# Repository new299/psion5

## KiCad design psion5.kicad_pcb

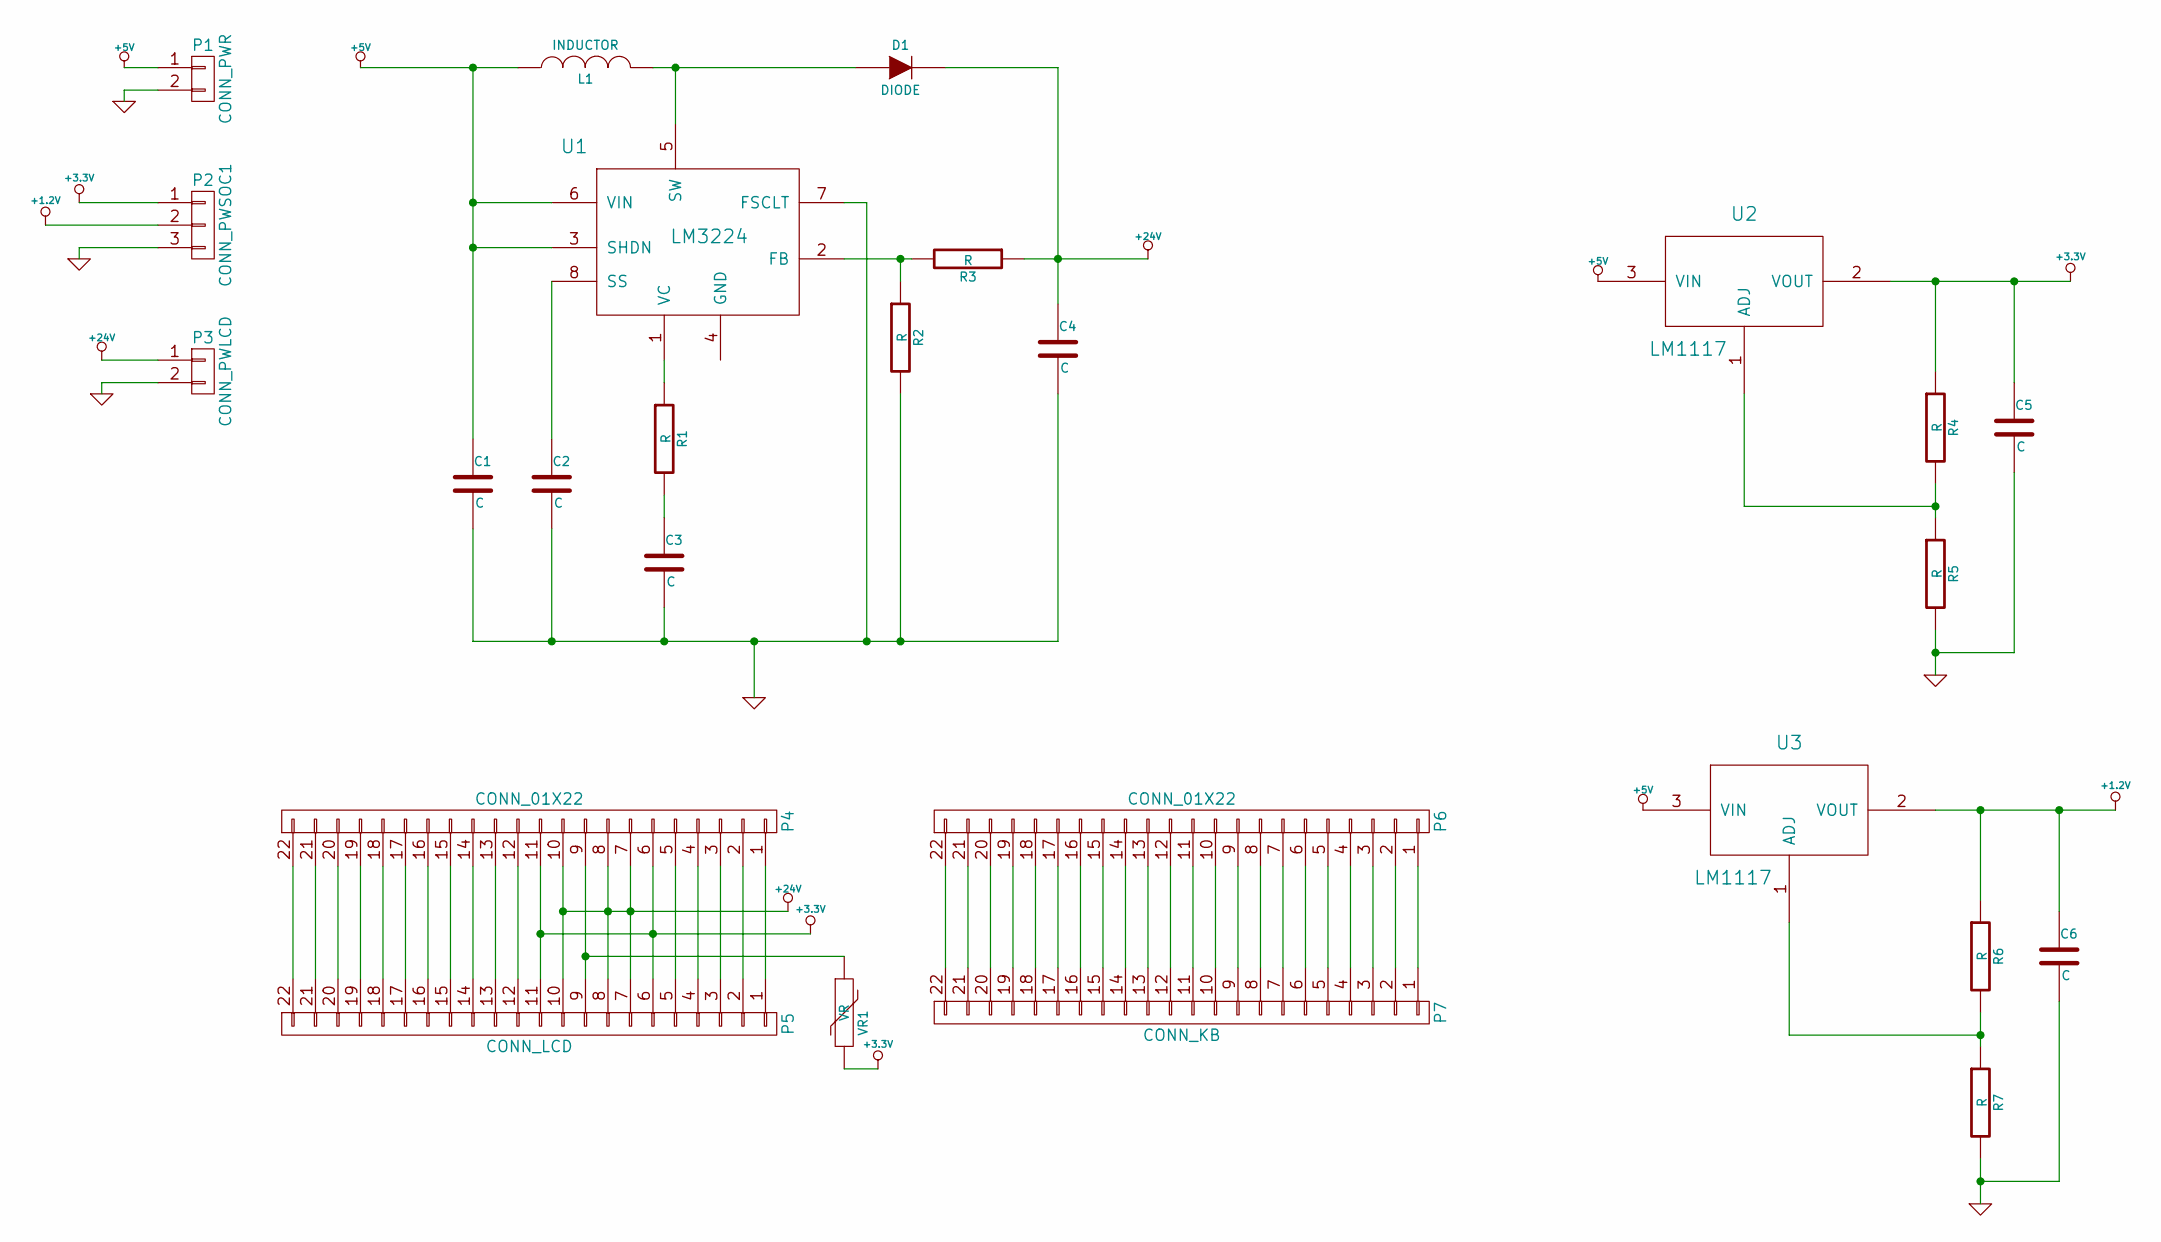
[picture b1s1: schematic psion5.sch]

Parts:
C1, C2, C3, C4, C5, C6: C; c_1206
D1: DIODE; Diode-MELF_Standard
L1: INDUCTOR; Neosid_Inductor_SMs42
P1: CONN_PWR; Socket_Strip_Straight_1x02
P2: CONN_PWSOC1; Socket_Strip_Straight_1x03
P3: CONN_PWLCD; Socket_Strip_Straight_1x02
P4, P6: CONN_01X22; Socket_Strip_Straight_1x22
P5: CONN_LCD; FPC22
P7: CONN_KB; FPC22
R1, R2, R3, R4, R5, R6, R7: R; R_1206
U1: LM3224; SSOP-8
U2, U3: LM1117; sot89
VR1: VR; R_1210

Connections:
+1.2V: C6.1, P2.2, R6.1, U3.2 (VOUT)
+3.3V: C5.1, P2.1, P4.6, P4.11, P5.6, P5.11, R4.1, U2.2 (VOUT), VR1.2
+5V: C1.1, L1.1, P1.1, U1.3 (SHDN), U1.6 (VIN), U2.3 (VIN), U3.3 (VIN)
+24V: C4.1, D1.2 (K), P3.1, P4.7, P4.8, P4.10, P5.7, P5.8, P5.10, R3.1
GND: C1.2, C2.2, C3.2, C4.2, C5.2, C6.2, P1.2, P2.3, P3.2, R2.2, R5.2, R7.2, U1.7 (FSCLT)
unnamed: C2.1, U1.8 (SS)
unnamed: C3.1, R1.2
unnamed: D1.1 (A), L1.2, U1.5 (SW)
unnamed: P4.1, P5.1
unnamed: P4.2, P5.2
unnamed: P4.3, P5.3
unnamed: P4.4, P5.4
unnamed: P4.5, P5.5
unnamed: P4.9, P5.9, VR1.1
unnamed: P4.12, P5.12
unnamed: P4.13, P5.13
unnamed: P4.14, P5.14
unnamed: P4.15, P5.15
unnamed: P4.16, P5.16
unnamed: P4.17, P5.17
unnamed: P4.18, P5.18
unnamed: P4.19, P5.19
unnamed: P4.20, P5.20
unnamed: P4.21, P5.21
unnamed: P4.22, P5.22
unnamed: P6.1, P7.1
unnamed: P6.2, P7.2
unnamed: P6.3, P7.3
unnamed: P6.4, P7.4
unnamed: P6.5, P7.5
unnamed: P6.6, P7.6
unnamed: P6.7, P7.7
unnamed: P6.8, P7.8
unnamed: P6.9, P7.9
unnamed: P6.10, P7.10
unnamed: P6.11, P7.11
unnamed: P6.12, P7.12
unnamed: P6.13, P7.13
unnamed: P6.14, P7.14
unnamed: P6.15, P7.15
unnamed: P6.16, P7.16
unnamed: P6.17, P7.17
unnamed: P6.18, P7.18
unnamed: P6.19, P7.19
unnamed: P6.20, P7.20
unnamed: P6.21, P7.21
unnamed: P6.22, P7.22
unnamed: R1.1, U1.1 (VC)
unnamed: R2.1, R3.2, U1.2 (FB)
unnamed: R4.2, R5.1, U2.1 (ADJ)
unnamed: R6.2, R7.1, U3.1 (ADJ)

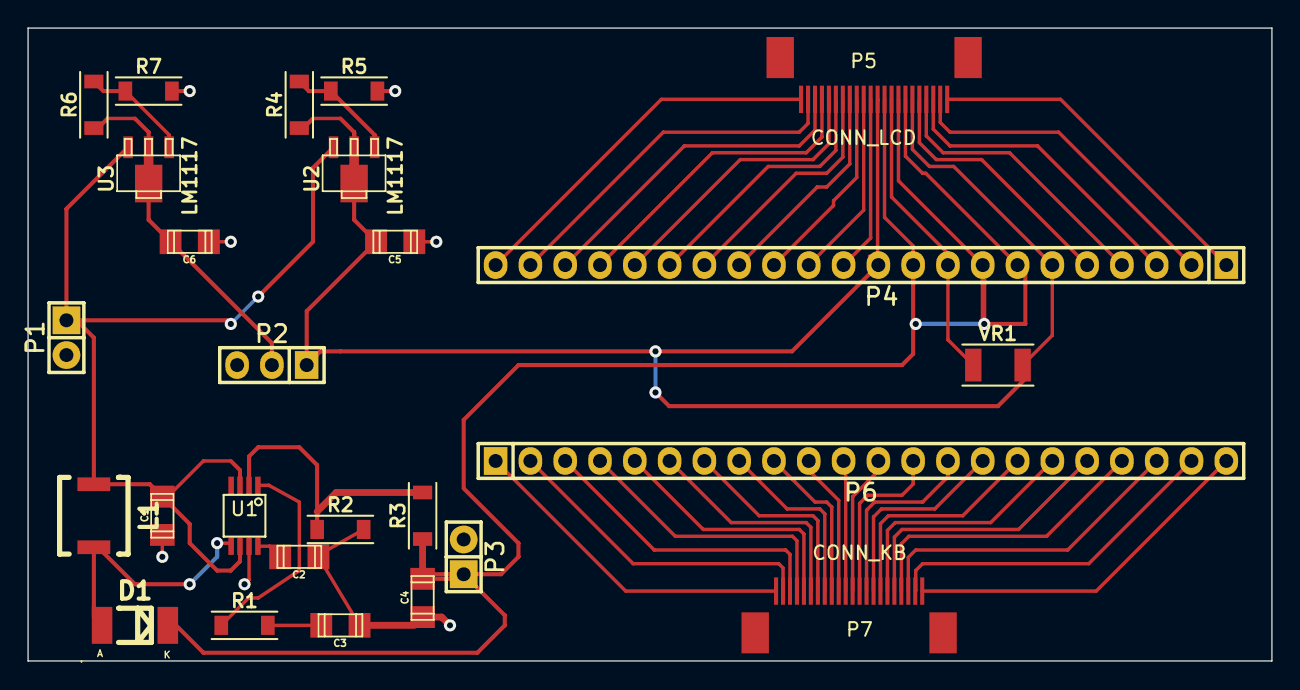
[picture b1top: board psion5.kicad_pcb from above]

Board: 2 copper layers, 90.8 x 46.2 mm, 26 parts (0 on the bottom side), 51 nets.

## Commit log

2014-09-06 as sent for fab
